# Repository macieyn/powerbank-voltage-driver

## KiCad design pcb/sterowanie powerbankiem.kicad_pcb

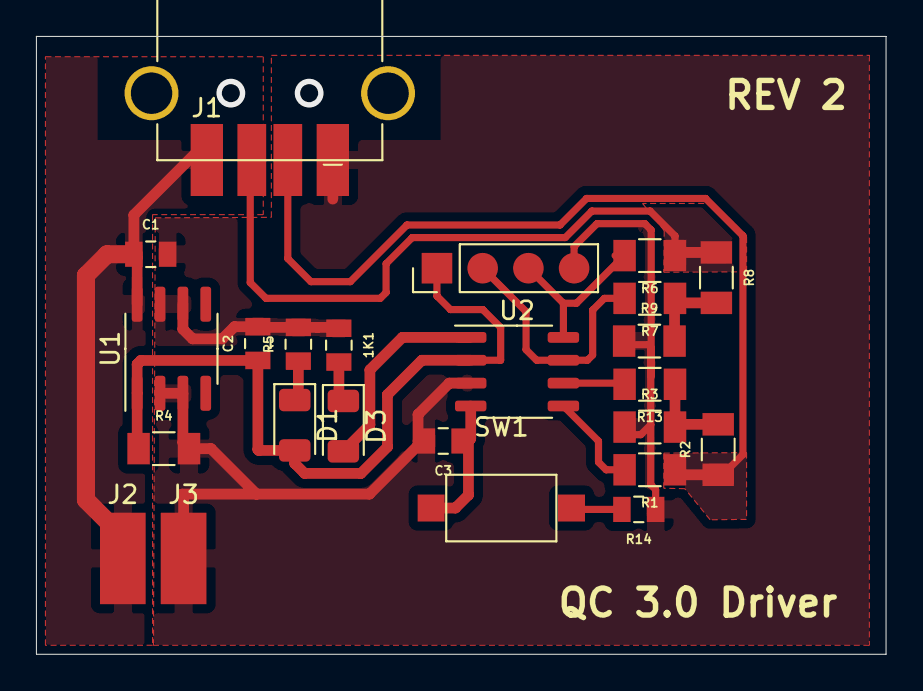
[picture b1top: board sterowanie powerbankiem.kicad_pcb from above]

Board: 2 copper layers, 47.2 x 34.3 mm, 24 parts (0 on the bottom side), 16 nets.

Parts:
1K1: R; R_0805
C1, C2: C; C_0805
C3: 1uF; C_0805
D1, D3: LED; LED_1206_3216Metric
J1: USB_A; USB_A_HORIZONTAL_SMD
J2: PAD_12V; SMDPAD_2,54x5,08
J3: PAD_GND; SMDPAD_2,54x5,08
J4: Conn_01x04; PinHeader_1x04_P2.54mm
R1, R6: 1K; R_1206
R2, R3, R8, R9: 2.7K; R_1206
R4: 150R; R_1206
R5: 1K; R_0805
R7, R13: 4.7K; R_1206
R14: 470R; R_0805
SW1: SW_DIP_x01; SW_SPST_CK_RS282G05A3
U1: L78L33_SO8; SOIC-8_3.9x4.9mm_P1.27mm
U2: STM32G030J6; SO-8_3.9x4.9mm_P1.27mm

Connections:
1: D3.2, U2.1
4: C3.1, SW1.1, U2.4
5: R1.2, U2.5
6: R13.2, U2.6
7: J4.2, R7.2, U2.7
8: J4.3, R6.2, U2.8
+3V3: C2.1, D1.2, J4.1, R4.1, U1.1, U2.2
+12V: C1.1, J1.1, J2.1, U1.8
D+: J1.3, R1.1, R2.1
D-: J1.2, R6.1, R8.1
GND: 1K1.1, C1.2, C2.2, C3.2, J1.4, J3.1, J4.4, R3.1, R4.2, R5.2, R9.1, R14.1, U1.2, U1.3, U1.6, U1.7, U2.3
unnamed: 1K1.2, D3.1
unnamed: D1.1, R5.1
unnamed: R7.1, R8.2, R9.2
unnamed: R2.2, R3.2, R13.1
unnamed: R14.2, SW1.2

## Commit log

2020-08-25 Wersja 1.1
2020-08-26 Wersja 1.2
2020-08-26 PCB STM32G030J6 compatible
2020-08-27 Drabinka rezystorowa (DAC) zamiast sterowania MOSFETami
2020-08-28 QC3 Controller, Button, Led Hal compatible libraries; Driver library
2020-10-12 Tested with PCB
2020-10-12 Resistors values better adjusted
